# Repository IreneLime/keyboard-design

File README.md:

This repo is the PCB design of an ergonomic keyboard.

Full Design:

PCB:

Firmware Code for this keyboard is located in: https://github.com/HWXLR8/qmk_firmware/tree/master/keyboards/irene

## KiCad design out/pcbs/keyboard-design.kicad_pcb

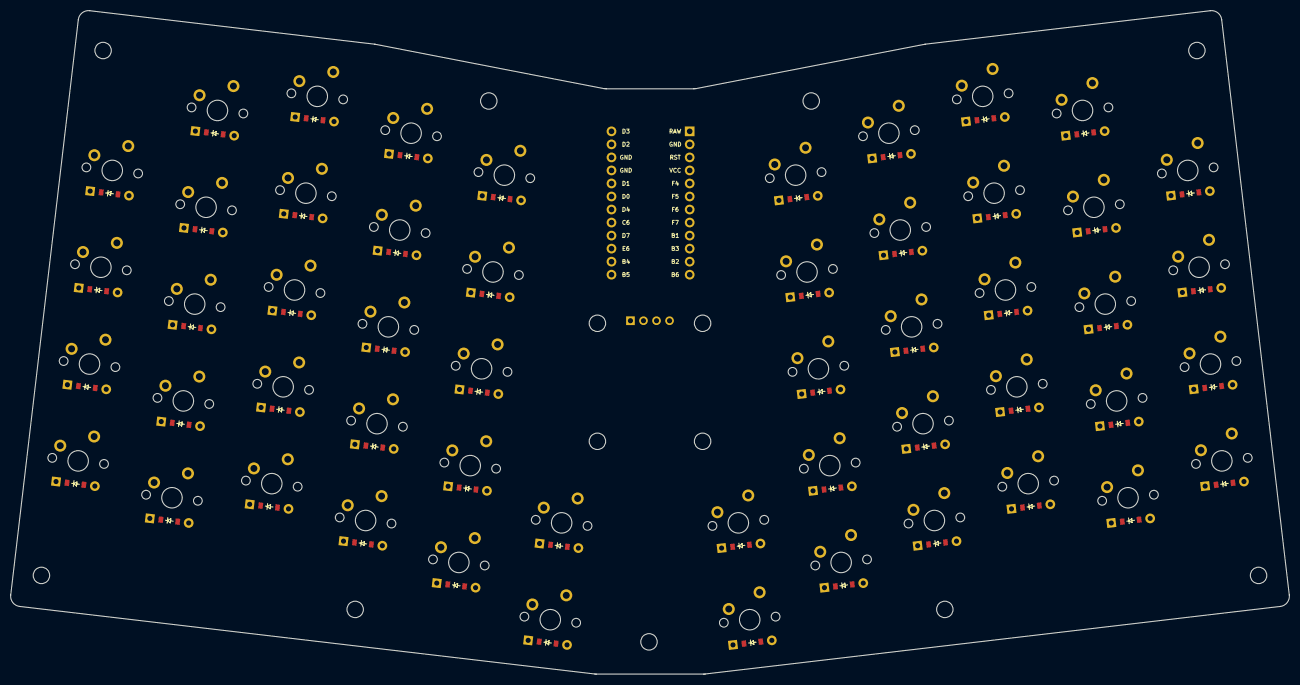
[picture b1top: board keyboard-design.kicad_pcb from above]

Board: 2 copper layers, 249.2 x 129.3 mm, 106 parts (0 on the bottom side), 72 nets, no tracks yet.

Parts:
D1, D2, D3, D4, D5, D6, D7, D8, D9, D10, D11, D12, D13, D14, D15, D16, D17, D18, D19, D20, D21, D22, D23, D24, D25, D26, D27, D28, D29, D30, D31, D32, D33, D34, D35, D36, D37, D38, D39, D40, D41, D42, D43, D44, D45, D46, D47, D48, D49, D50, D51, D52: ComboDiode
MCU1: ProMicro
OLED1: OLED; OLED_headers
S1, S2, S3, S4, S5, S6, S7, S8, S9, S10, S11, S12, S13, S14, S15, S16, S17, S18, S19, S20, S21, S22, S23, S24, S25, S26, S27, S28, S29, S30, S31, S32, S33, S34, S35, S36, S37, S38, S39, S40, S41, S42, S43, S44, S45, S46, S47, S48, S49, S50, S51, S52: MX

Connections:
B1: MCU1.9, S47.2, S48.2, S49.2, S50.2, S51.2, S52.2
B2: D2.1, D7.1, D12.1, D17.1, D22.1, D28.1, D33.1, D38.1, D43.1, D48.1, MCU1.11
B3: D3.1, D8.1, D13.1, D18.1, D23.1, D29.1, D34.1, D39.1, D44.1, D49.1, MCU1.10
B4: D1.1, D6.1, D11.1, D16.1, D21.1, D27.1, D32.1, D37.1, D42.1, D47.1, MCU1.23
B5: D25.1, D51.1, MCU1.24
B6: D4.1, D9.1, D14.1, D19.1, D24.1, D30.1, D35.1, D40.1, D45.1, D50.1, MCU1.12
C6: MCU1.20, S16.2, S17.2, S18.2, S19.2, S20.2
D0: MCU1.18, OLED1.3
D1: MCU1.17, OLED1.4
D2: MCU1.14, S1.2, S2.2, S3.2, S4.2, S5.2
D3: MCU1.13, S6.2, S7.2, S8.2, S9.2, S10.2
D4: MCU1.19, S11.2, S12.2, S13.2, S14.2, S15.2
D7: MCU1.21, S21.2, S22.2, S23.2, S24.2, S25.2, S26.2
E6: D5.1, D10.1, D15.1, D20.1, D26.1, D31.1, D36.1, D41.1, D46.1, D52.1, MCU1.22
F4: MCU1.5, S27.2, S28.2, S29.2, S30.2, S31.2
F5: MCU1.6, S32.2, S33.2, S34.2, S35.2, S36.2
F6: MCU1.7, S37.2, S38.2, S39.2, S40.2, S41.2
F7: MCU1.8, S42.2, S43.2, S44.2, S45.2, S46.2
GND: MCU1.2, MCU1.15, MCU1.16, OLED1.1
VCC: MCU1.4, OLED1.2
index_bottom: D15.2, S15.1
index_home: D16.2, S16.1
index_mid: D17.2, S17.1
index_num: D19.2, S19.1
index_top: D18.2, S18.1
inner_bottom: D20.2, S20.1
inner_home: D21.2, S21.1
inner_mid: D22.2, S22.1
inner_num: D24.2, S24.1
inner_top: D23.2, S23.1
middle_bottom: D10.2, S10.1
middle_home: D11.2, S11.1
middle_mid: D12.2, S12.1
middle_num: D14.2, S14.1
middle_top: D13.2, S13.1
mirror_index_bottom: D41.2, S41.1
mirror_index_home: D42.2, S42.1
mirror_index_mid: D43.2, S43.1
mirror_index_num: D45.2, S45.1
mirror_index_top: D44.2, S44.1
mirror_inner_bottom: D46.2, S46.1
mirror_inner_home: D47.2, S47.1
mirror_inner_mid: D48.2, S48.1
mirror_inner_num: D50.2, S50.1
mirror_inner_top: D49.2, S49.1
mirror_middle_bottom: D36.2, S36.1
mirror_middle_home: D37.2, S37.1
mirror_middle_mid: D38.2, S38.1
mirror_middle_num: D40.2, S40.1
mirror_middle_top: D39.2, S39.1
mirror_pinky_home: D27.2, S27.1
mirror_pinky_mid: D28.2, S28.1
mirror_pinky_num: D30.2, S30.1
mirror_pinky_top: D29.2, S29.1
mirror_ring_bottom: D31.2, S31.1
mirror_ring_home: D32.2, S32.1
mirror_ring_mid: D33.2, S33.1
mirror_ring_num: D35.2, S35.1
mirror_ring_top: D34.2, S34.1
mirror_thumb_bottom: D52.2, S52.1
mirror_thumb_bottom_thumb: D51.2, S51.1
pinky_home: D1.2, S1.1
pinky_mid: D2.2, S2.1
pinky_num: D4.2, S4.1
pinky_top: D3.2, S3.1
ring_bottom: D5.2, S5.1
ring_home: D6.2, S6.1
ring_mid: D7.2, S7.1
ring_num: D9.2, S9.1
ring_top: D8.2, S8.1
thumb_bottom: D26.2, S26.1
thumb_bottom_thumb: D25.2, S25.1

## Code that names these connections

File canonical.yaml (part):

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    autobind: 10
    skip: false
    asym: both
    colrow: pinky_home
    name: matrix_pinky_home
    column_net: D2
    mirror:
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    autobind: 10
    skip: false
    asym: both
    colrow: pinky_top
    name: matrix_pinky_top
    column_net: D2
    mirror:
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    autobind: 10
    skip: false
    asym: both
    colrow: pinky_num
    name: matrix_pinky_num
    column_net: D2
    mirror:
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    autobind: 10
    skip: false
    asym: both
    colrow: pinky_mid
    name: matrix_pinky_mid
    column_net: D2
    mirror:
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    autobind: 10
    skip: false
    asym: both
    colrow: mirror_pinky_home
    name: mirror_matrix_pinky_home
    column_net: F4
    mirror:
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    autobind: 10
    skip: false
    asym: both
    colrow: mirror_pinky_top
    name: mirror_matrix_pinky_top
    column_net: F4
    mirror:
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    autobind: 10
    skip: false
    asym: both
    colrow: mirror_pinky_num
    name: mirror_matrix_pinky_num
    column_net: F4
    mirror:
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    autobind: 10
    skip: false
    asym: both
    colrow: mirror_pinky_mid
    name: mirror_matrix_pinky_mid
    column_net: F4
    mirror:
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
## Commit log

2024-03-19 Create makefile
2024-03-19 submodule
2024-03-20 output
2024-03-20 Update keyboard_layout.yaml yay
2024-03-20 Update keyboard_layout.yaml fix border
2024-03-21 Add mounting holes
2024-03-21 Finished mounting hole placement
2024-03-22 Added silkscreen & Make text invisible
2024-03-25 Refill
2025-01-13 Add descriptions in README.md
2025-10-22 Update README.md
    Add PCB image
